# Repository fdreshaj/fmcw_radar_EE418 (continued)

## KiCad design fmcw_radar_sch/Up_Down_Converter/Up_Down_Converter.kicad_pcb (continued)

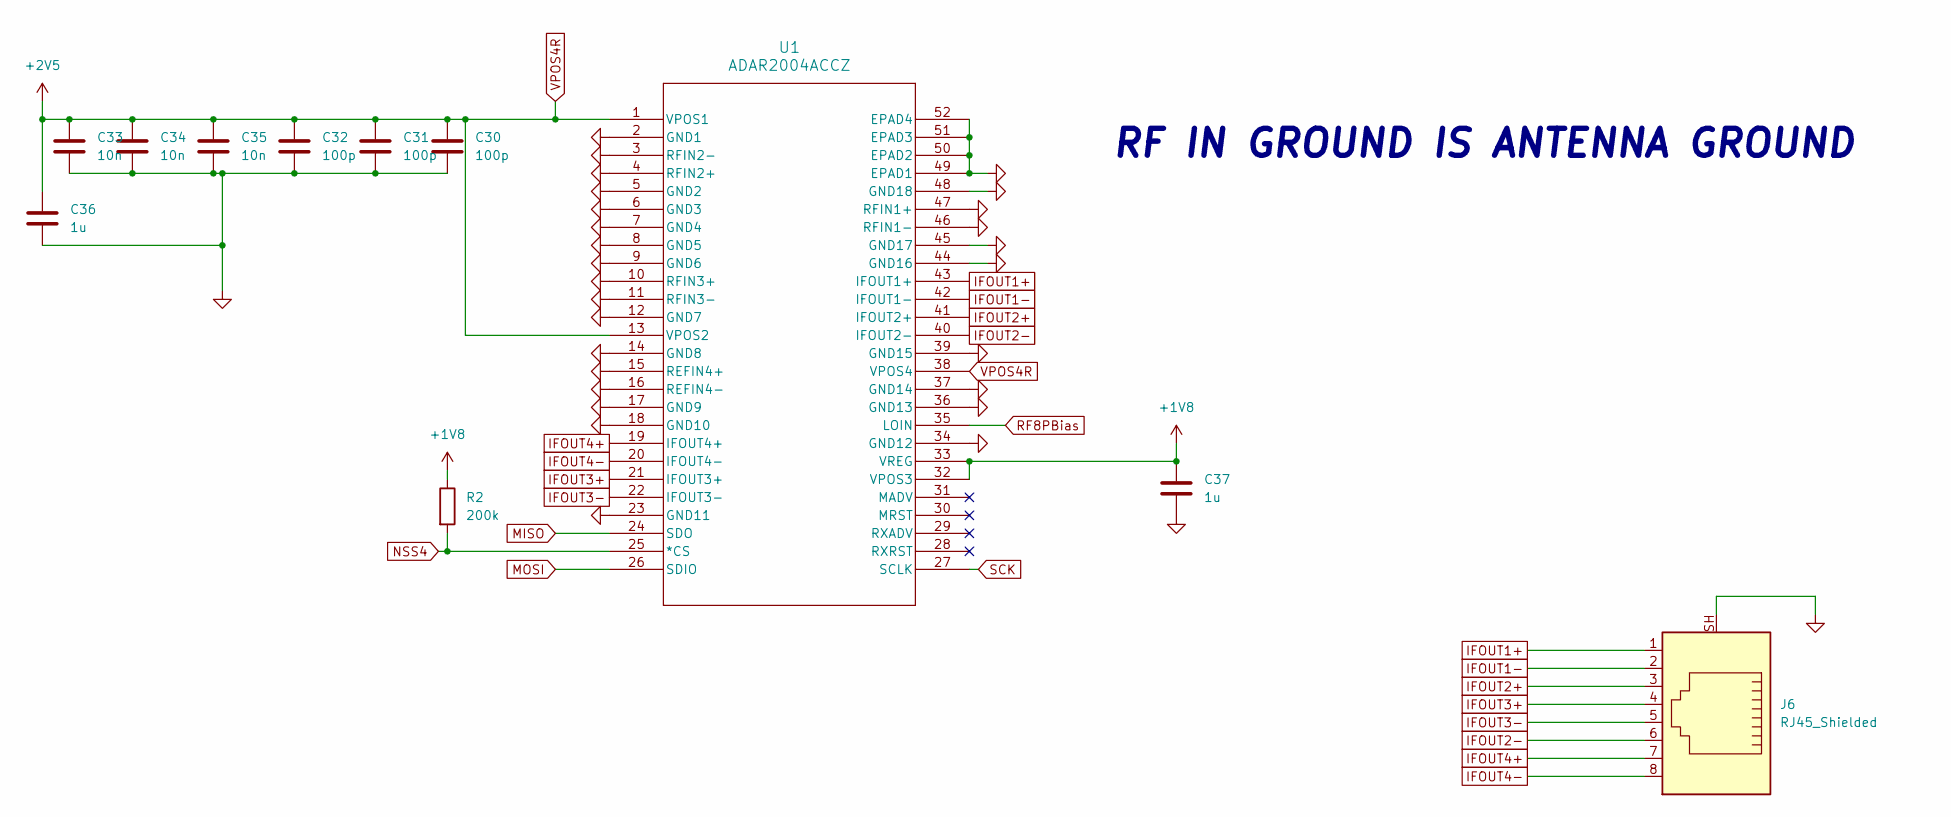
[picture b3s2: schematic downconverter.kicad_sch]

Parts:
C30, C31, C32: 100p; C_0603_1608Metric_Pad1.08x0.95mm_HandSolder
C33, C34, C35: 10n; C_0603_1608Metric_Pad1.08x0.95mm_HandSolder
C36, C37: 1u; C_0603_1608Metric_Pad1.08x0.95mm_HandSolder
J6: RJ45_Shielded; RJ45_Amphenol_RJHSE5380
R2: 200k; R_0603_1608Metric_Pad0.98x0.95mm_HandSolder
U1: ADAR2004ACCZ; LGA_CC_48_2_ADI

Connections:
+1V8: C37.1, R2.1, U1.32 (VPOS3), U1.33 (VREG); also elsewhere on the board
GND: C30.2, C31.2, C32.2, C33.2, C34.2, C35.2, C36.2, C37.2, J6.SH, U1.2 (GND1), U1.3 (RFIN2-), U1.4 (RFIN2+), U1.5 (GND2), U1.6 (GND3), U1.7 (GND4), U1.8 (GND5), U1.9 (GND6), U1.10 (RFIN3+), U1.11 (RFIN3-), U1.12 (GND7), U1.14 (GND8), U1.15 (REFIN4+), U1.16 (REFIN4-), U1.17 (GND9), U1.18 (GND10), U1.23 (GND11), U1.34 (GND12), U1.36 (GND13), U1.37 (GND14), U1.39 (GND15), U1.44 (GND16), U1.45 (GND17), U1.46 (RFIN1-), U1.47 (RFIN1+), U1.48 (GND18), U1.49 (EPAD1), U1.50 (EPAD2), U1.51 (EPAD3), U1.52 (EPAD4); also elsewhere on the board
IFOUT1+: J6.1, U1.43 (IFOUT1+)
IFOUT1-: J6.2, U1.42 (IFOUT1-)
IFOUT2+: J6.3, U1.41 (IFOUT2+)
IFOUT2-: J6.6, U1.40 (IFOUT2-)
IFOUT3+: J6.4, U1.21 (IFOUT3+)
IFOUT3-: J6.5, U1.22 (IFOUT3-)
IFOUT4+: J6.7, U1.19 (IFOUT4+)
IFOUT4-: J6.8, U1.20 (IFOUT4-)
MISO: U1.24 (SDO); also elsewhere on the board
MOSI: U1.26 (SDIO); also elsewhere on the board
NSS4: R2.2, U1.25 (*CS); also elsewhere on the board
SCK: U1.27 (SCLK); also elsewhere on the board
VPOS4R: C30.1, C31.1, C32.1, C33.1, C34.1, C35.1, C36.1, U1.1 (VPOS1), U1.13 (VPOS2), U1.38 (VPOS4); also elsewhere on the board

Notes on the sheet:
RF IN GROUND IS ANTENNA GROUND

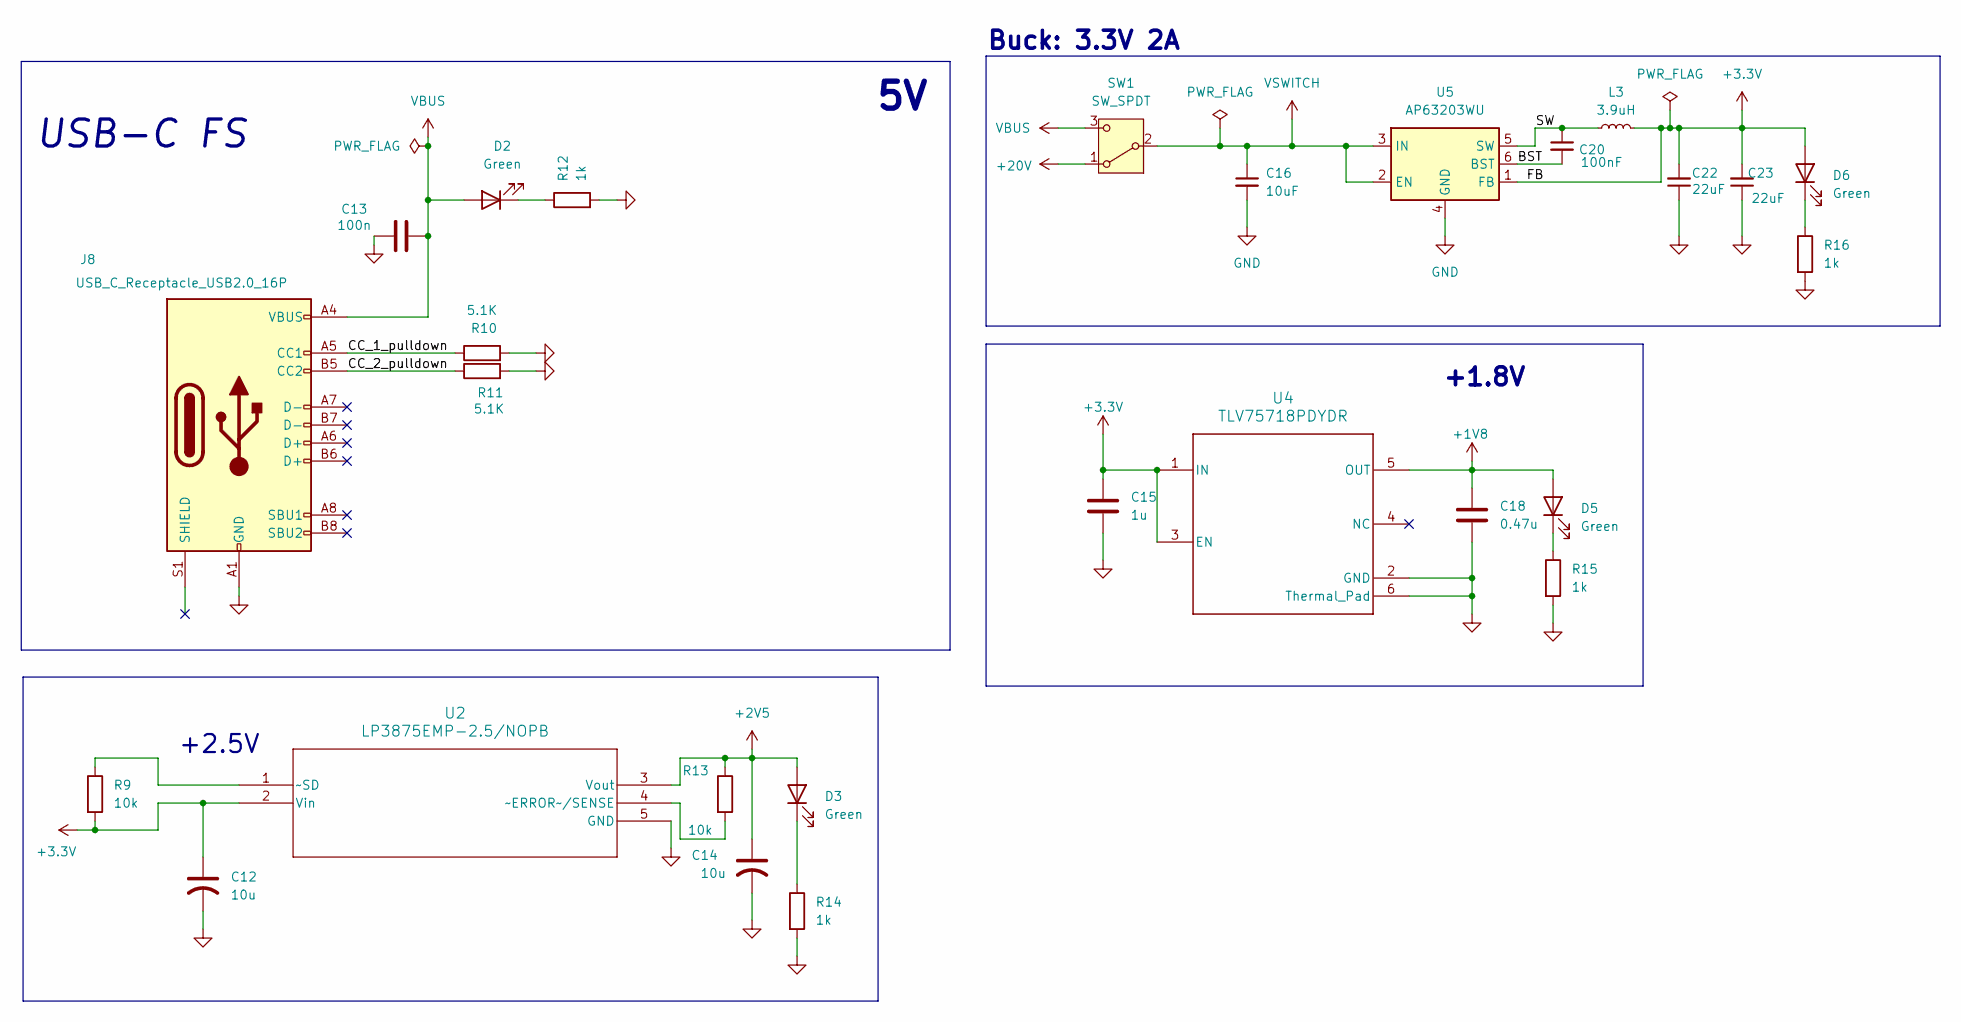
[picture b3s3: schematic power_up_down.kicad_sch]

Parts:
C12, C14: 10u; C_0603_1608Metric_Pad1.08x0.95mm_HandSolder
C13: 100n; C_0603_1608Metric_Pad1.08x0.95mm_HandSolder
C15: 1u; C_0603_1608Metric_Pad1.08x0.95mm_HandSolder
C16: 10uF; C_0603_1608Metric_Pad1.08x0.95mm_HandSolder
C18: 0.47u; C_0603_1608Metric_Pad1.08x0.95mm_HandSolder
C20: 100nF; C_0603_1608Metric_Pad1.08x0.95mm_HandSolder
C22, C23: 22uF; C_0603_1608Metric_Pad1.08x0.95mm_HandSolder
D2, D3, D5, D6: Green; LED_0603_1608Metric_Pad1.05x0.95mm_HandSolder
J8: USB_C_Receptacle_USB2.0_16P; USB_C_Receptacle_G-Switch_GT-USB-7010ASV
L3: 3.9uH; L_Bourns_SDR0604
R9, R13: 10k; R_1206_3216Metric_Pad1.30x1.75mm_HandSolder
R10, R11: 5.1K; R_0603_1608Metric_Pad0.98x0.95mm_HandSolder
R12, R14, R15, R16: 1k; R_0603_1608Metric_Pad0.98x0.95mm_HandSolder
SW1: SW_SPDT; SW_Slide_SPDT_Straight_CK_OS102011MS2Q
U2: LP3875EMP-2.5/NOPB; DNT12_TEX
U4: TLV75718PDYDR; DYD0005A-MFG
U5: AP63203WU; TSOT-23-6

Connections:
+1V8: C18.1, D5.2 (A), U4.5 (OUT); also elsewhere on the board
+3.3V: C12.1, C15.1, C22.2, C23.2, D6.2 (A), L3.2, R9.2, U2.2 (Vin), U4.1 (IN), U4.3 (EN), U5.1 (FB)
+20V: SW1.1 (A); also elsewhere on the board
/Power/BST: C20.2, U5.6 (BST)
/Power/CC_1_pulldown: J8.A5 (CC1), R10.1
/Power/CC_2_pulldown: J8.B5 (CC2), R11.1
/Power/SW: C20.1, L3.1, U5.5 (SW)
GND: C12.2, C13.1, C14.2, C15.2, C16.2, C18.2, C22.1, C23.1, J8.A1 (GND), J8.A12 (GND), J8.B1 (GND), J8.B12 (GND), R10.2, R11.2, R12.2, R14.2, R15.2, R16.2, U2.5 (GND), U4.2 (GND), U4.6 (Thermal_Pad), U5.4 (GND); also elsewhere on the board
unnamed: D2.1 (K), R12.1
unnamed: D3.1 (K), R14.1
unnamed: D5.1 (K), R15.1
unnamed: D6.1 (K), R16.1
unnamed: R13.2, U2.4 (~ERROR~/SENSE)
unnamed: R9.1, U2.1 (~SD)
VBUS: C13.2, D2.2 (A), J8.A4 (VBUS), J8.A9 (VBUS), J8.B4 (VBUS), J8.B9 (VBUS), SW1.3 (C)
VPOS4R: C14.1, D3.2 (A), R13.1, U2.3 (Vout); also elsewhere on the board
VSWITCH: C16.1, SW1.2 (B), U5.2 (EN), U5.3 (IN); also elsewhere on the board

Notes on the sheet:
Buck: 3.3V 2A
+2.5V
USB-C FS
+1.8V

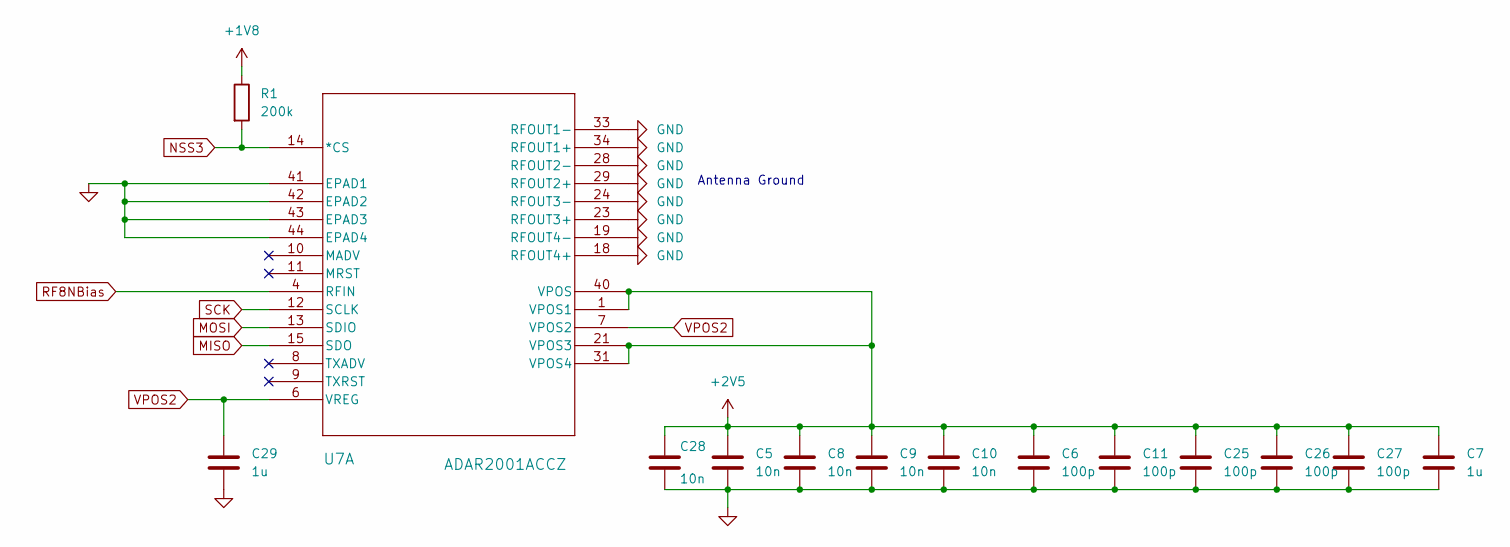
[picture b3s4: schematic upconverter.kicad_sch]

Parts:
C5, C8, C9, C10, C28: 10n; C_0603_1608Metric_Pad1.08x0.95mm_HandSolder
C6, C11, C25, C26, C27: 100p; C_0603_1608Metric_Pad1.08x0.95mm_HandSolder
C7, C29: 1u; C_0603_1608Metric_Pad1.08x0.95mm_HandSolder
R1: 200k; R_0603_1608Metric_Pad0.98x0.95mm_HandSolder
U7: ADAR2001ACCZ; LGA-CC-40-7_ADI

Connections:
+1V8: R1.1; also elsewhere on the board
GND: C5.2, C6.2, C7.2, C8.2, C9.2, C10.2, C11.2, C25.2, C26.2, C27.2, C28.2, C29.2, U7.18 (RFOUT4+), U7.19 (RFOUT4-), U7.23 (RFOUT3+), U7.24 (RFOUT3-), U7.28 (RFOUT2-), U7.29 (RFOUT2+), U7.33 (RFOUT1-), U7.34 (RFOUT1+), U7.41 (EPAD1), U7.42 (EPAD2), U7.43 (EPAD3), U7.44 (EPAD4); also elsewhere on the board
MISO: U7.15 (SDO); also elsewhere on the board
MOSI: U7.13 (SDIO); also elsewhere on the board
NSS3: R1.2, U7.14 (*CS); also elsewhere on the board
SCK: U7.12 (SCLK); also elsewhere on the board
VPOS2: C29.1, U7.6 (VREG), U7.7 (VPOS2)
VPOS4R: C5.1, C6.1, C7.1, C8.1, C9.1, C10.1, C11.1, C25.1, C26.1, C27.1, C28.1, U7.1 (VPOS1), U7.21 (VPOS3), U7.31 (VPOS4), U7.40 (VPOS); also elsewhere on the board

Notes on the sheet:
Antenna Ground

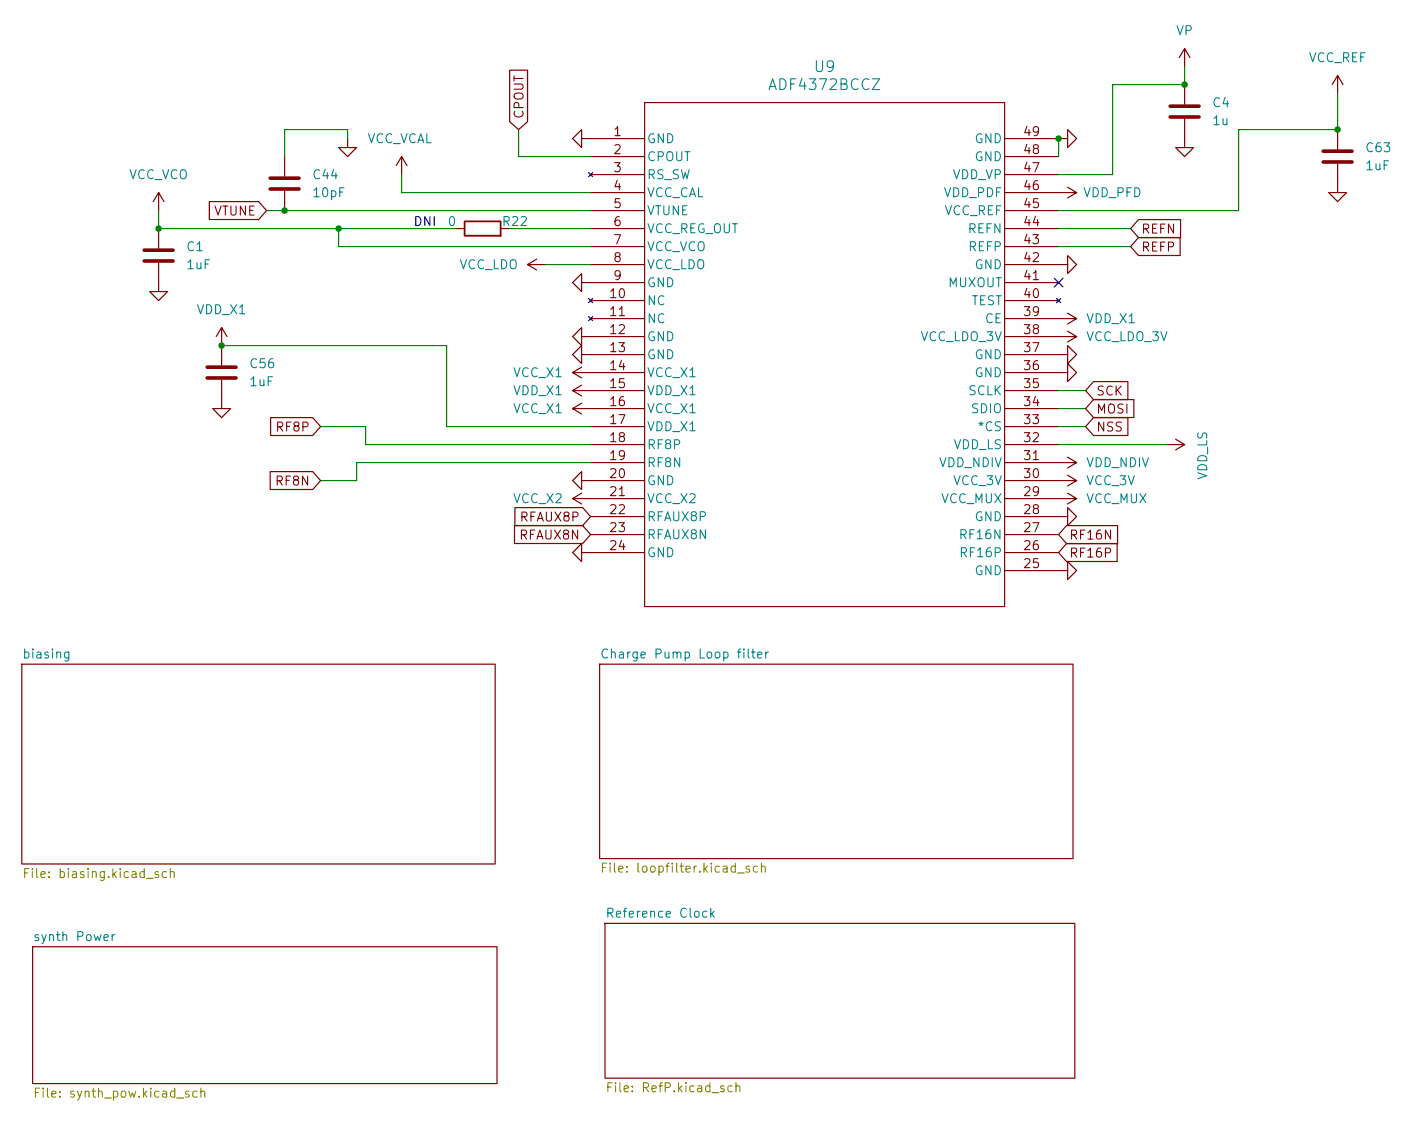
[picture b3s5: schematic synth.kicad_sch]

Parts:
C1, C56, C63: 1uF; C_0603_1608Metric_Pad1.08x0.95mm_HandSolder
C4: 1u; C_0603_1608Metric_Pad1.08x0.95mm_HandSolder
C44: 10pF; C_0603_1608Metric_Pad1.08x0.95mm_HandSolder
R22: 0; R_0603_1608Metric_Pad0.98x0.95mm_HandSolder
U9: ADF4372BCCZ; CC-48-4_ADI

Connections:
CPOUT: U9.2 (CPOUT); also elsewhere on the board
GND: C1.2, C4.2, C44.1, C56.2, C63.2, U9.1 (GND), U9.9 (GND), U9.12 (GND), U9.13 (GND), U9.20 (GND), U9.24 (GND), U9.25 (GND), U9.28 (GND), U9.36 (GND), U9.37 (GND), U9.42 (GND), U9.48 (GND), U9.49 (GND); also elsewhere on the board
MOSI: U9.34 (SDIO); also elsewhere on the board
NSS: U9.33 (*CS); also elsewhere on the board
unnamed: R22.2, U9.6 (VCC_REG_OUT)
REFP: U9.43 (REFP); also elsewhere on the board
RF16N: U9.27 (RF16N); also elsewhere on the board
RF16P: U9.26 (RF16P); also elsewhere on the board
RFAUX8N: U9.23 (RFAUX8N); also elsewhere on the board
RFAUX8P: U9.22 (RFAUX8P); also elsewhere on the board
SCK: U9.35 (SCLK); also elsewhere on the board
VCC_3V: C56.1, U9.4 (VCC_CAL), U9.14 (VCC_X1), U9.15 (VDD_X1), U9.16 (VCC_X1), U9.17 (VDD_X1), U9.21 (VCC_X2), U9.29 (VCC_MUX), U9.30 (VCC_3V), U9.31 (VDD_NDIV), U9.32 (VDD_LS), U9.39 (CE); also elsewhere on the board
VCC_LDO: U9.8 (VCC_LDO); also elsewhere on the board
VCC_LDO_3V: C4.1, C63.1, U9.38 (VCC_LDO_3V), U9.45 (VCC_REF), U9.46 (VDD_PDF), U9.47 (VDD_VP); also elsewhere on the board
VCC_VCO: C1.1, R22.1, U9.7 (VCC_VCO); also elsewhere on the board
VTUNE: C44.2, U9.5 (VTUNE); also elsewhere on the board

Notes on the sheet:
DNI

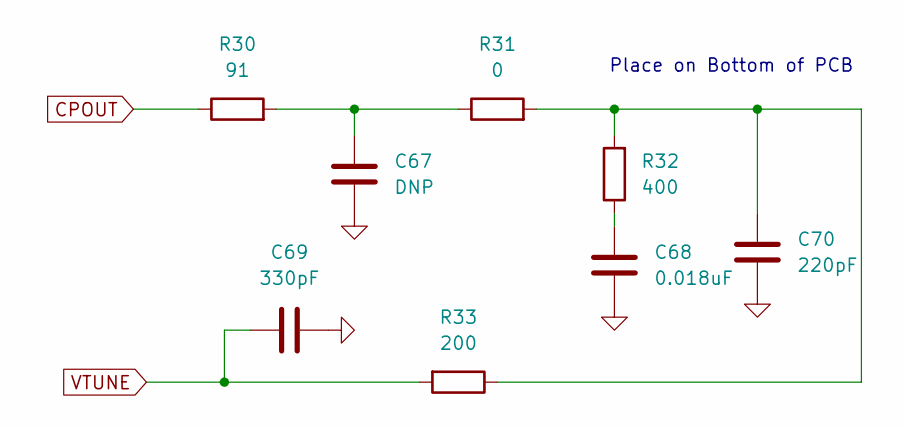
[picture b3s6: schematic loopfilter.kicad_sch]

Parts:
C67: DNP; C_0603_1608Metric_Pad1.08x0.95mm_HandSolder
C68: 0.018uF; C_0603_1608Metric_Pad1.08x0.95mm_HandSolder
C69: 330pF; C_0603_1608Metric_Pad1.08x0.95mm_HandSolder
C70: 220pF; C_0603_1608Metric_Pad1.08x0.95mm_HandSolder
R30: 91; R_0603_1608Metric_Pad0.98x0.95mm_HandSolder
R31: 0; R_0603_1608Metric_Pad0.98x0.95mm_HandSolder
R32: 400; R_0603_1608Metric_Pad0.98x0.95mm_HandSolder
R33: 200; R_0603_1608Metric_Pad0.98x0.95mm_HandSolder

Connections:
CPOUT: R30.1; also elsewhere on the board
GND: C67.2, C68.2, C69.2, C70.2; also elsewhere on the board
unnamed: C67.1, R30.2, R31.1
unnamed: C68.1, R32.1
unnamed: C70.1, R31.2, R32.2, R33.1
VTUNE: C69.1, R33.2; also elsewhere on the board

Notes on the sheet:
Place on Bottom of PCB

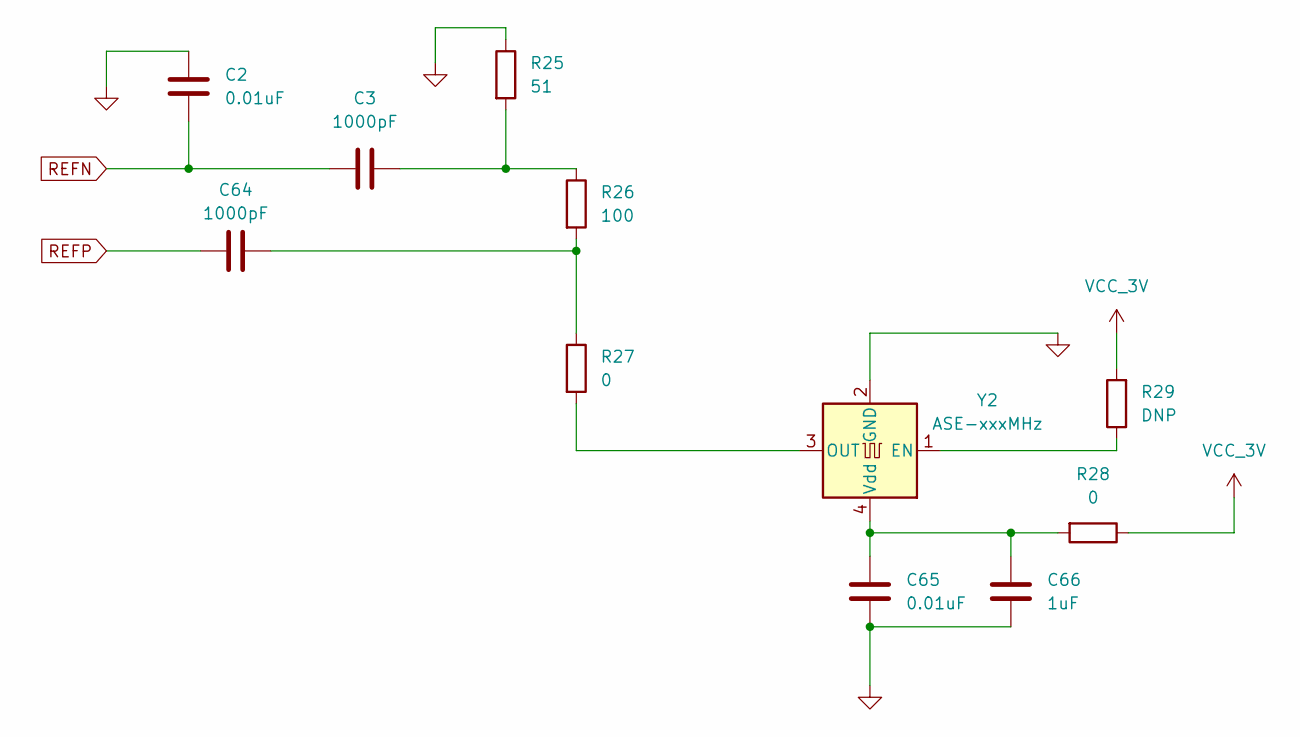
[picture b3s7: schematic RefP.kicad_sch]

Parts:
C2, C65: 0.01uF; C_0603_1608Metric_Pad1.08x0.95mm_HandSolder
C3, C64: 1000pF; C_0603_1608Metric_Pad1.08x0.95mm_HandSolder
C66: 1uF; C_0603_1608Metric_Pad1.08x0.95mm_HandSolder
R25: 51; R_0603_1608Metric_Pad0.98x0.95mm_HandSolder
R26: 100; R_0603_1608Metric_Pad0.98x0.95mm_HandSolder
R27, R28: 0; R_0603_1608Metric_Pad0.98x0.95mm_HandSolder
R29: DNP; R_0603_1608Metric_Pad0.98x0.95mm_HandSolder
Y2: ASE-xxxMHz; Oscillator_SMD_Abracon_ASE-4Pin_3.2x2.5mm

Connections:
GND: C2.1, C65.2, C66.2, R25.1, Y2.2 (GND); also elsewhere on the board
unnamed: C64.1, R26.2, R27.1
unnamed: R29.1, Y2.1 (EN)
unnamed: R27.2, Y2.3 (OUT)
unnamed: C65.1, C66.1, R28.2, Y2.4 (Vdd)
REFP: C64.2; also elsewhere on the board
VCC_3V: R28.1, R29.2; also elsewhere on the board

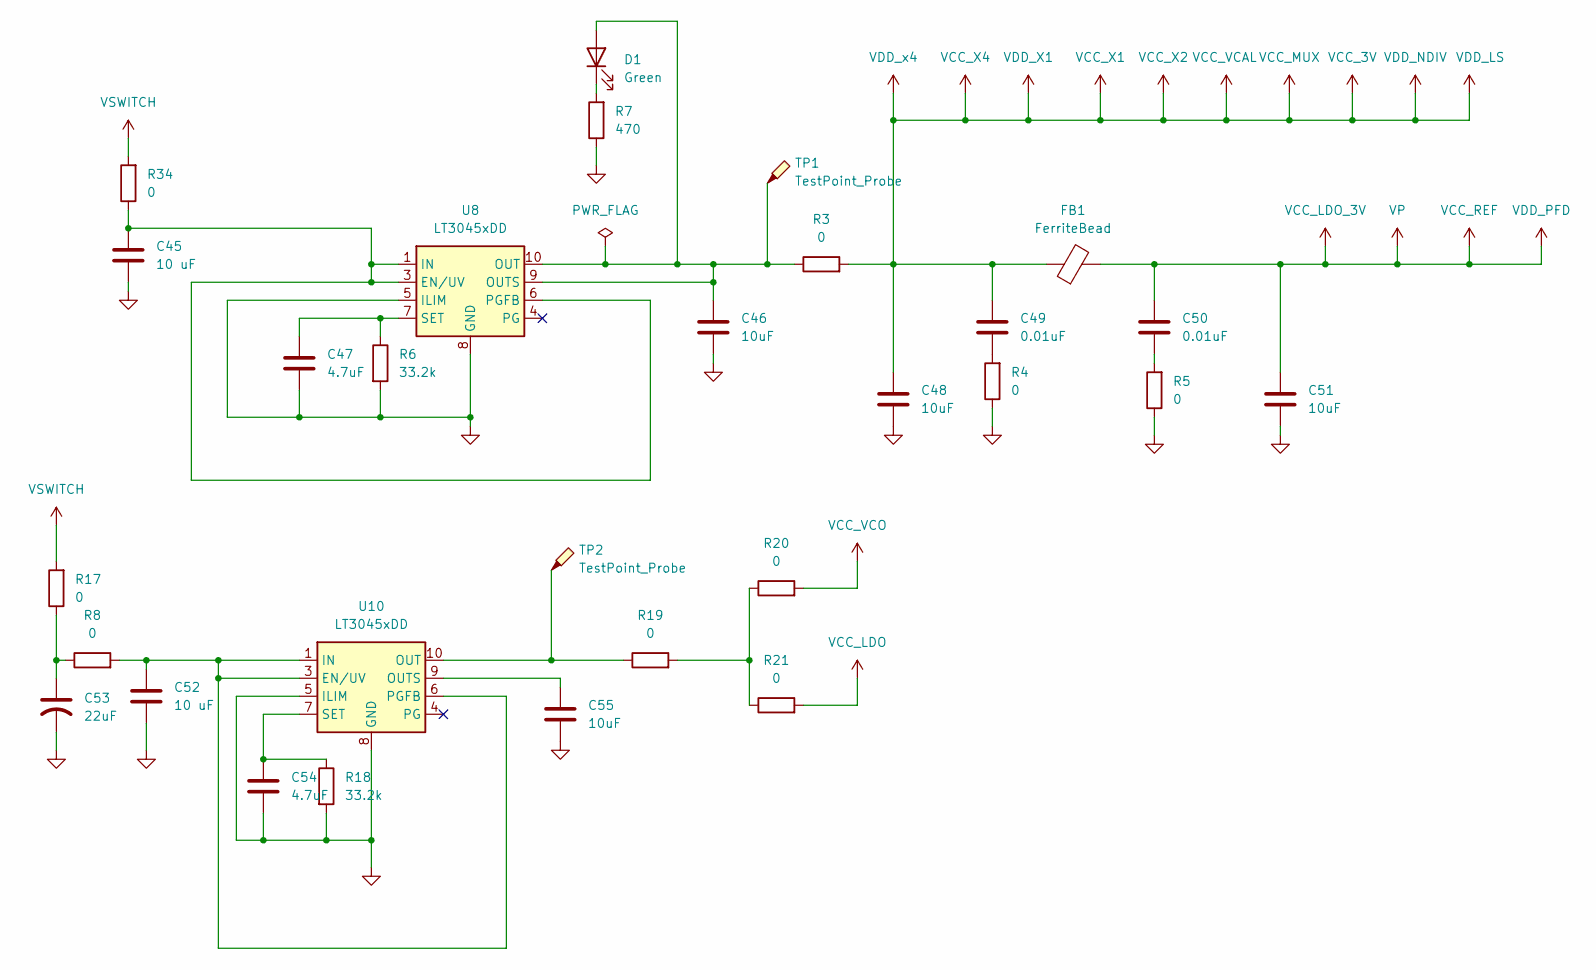
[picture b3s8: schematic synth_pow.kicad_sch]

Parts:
C45, C52: 10 uF; C_0603_1608Metric_Pad1.08x0.95mm_HandSolder
C46, C48, C51, C55: 10uF; C_0603_1608Metric_Pad1.08x0.95mm_HandSolder
C47, C54: 4.7uF; C_0603_1608Metric_Pad1.08x0.95mm_HandSolder
C49, C50: 0.01uF; C_0603_1608Metric_Pad1.08x0.95mm_HandSolder
C53: 22uF; C_0603_1608Metric_Pad1.08x0.95mm_HandSolder
D1: Green; LED_0603_1608Metric_Pad1.05x0.95mm_HandSolder
FB1: FerriteBead; L_0603_1608Metric_Pad1.05x0.95mm_HandSolder
R3, R4, R5, R8, R17, R19, R20, R21, R34: 0; R_0603_1608Metric_Pad0.98x0.95mm_HandSolder
R6, R18: 33.2k; R_0603_1608Metric_Pad0.98x0.95mm_HandSolder
R7: 470; R_0603_1608Metric_Pad0.98x0.95mm_HandSolder
TP1, TP2: TestPoint_Probe; TestPoint_Loop_D2.50mm_Drill1.0mm
U8, U10: LT3045xDD; DFN-10-1EP_3x3mm_P0.5mm_EP1.65x2.38mm

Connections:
GND: C45.2, C46.2, C47.2, C48.2, C51.2, C52.2, C53.2, C54.2, C55.2, R4.1, R5.1, R6.2, R7.1, R18.2, U8.5 (ILIM), U8.8 (GND), U8.11 (GND), U10.5 (ILIM), U10.8 (GND), U10.11 (GND); also elsewhere on the board
unnamed: C49.2, R4.2
unnamed: C50.2, R5.2
unnamed: C53.1, R8.1, R17.1
unnamed: C46.1, D1.2 (A), R3.1, TP1.1, U8.9 (OUTS), U8.10 (OUT)
unnamed: D1.1 (K), R7.2
unnamed: R19.2, R20.1, R21.1
unnamed: C45.1, R34.1, U8.1 (IN), U8.2 (IN), U8.3 (EN/UV), U8.6 (PGFB)
unnamed: C47.1, R6.1, U8.7 (SET)
unnamed: C52.1, R8.2, U10.1 (IN), U10.2 (IN), U10.3 (EN/UV), U10.6 (PGFB)
unnamed: R19.1, TP2.1, U10.10 (OUT)
unnamed: C55.1, U10.9 (OUTS)
unnamed: C54.1, R18.1, U10.7 (SET)
VCC_3V: C48.1, C49.1, FB1.1, R3.2; also elsewhere on the board
VCC_LDO: R21.2; also elsewhere on the board
VCC_LDO_3V: C50.1, C51.1, FB1.2; also elsewhere on the board
VCC_VCO: R20.2; also elsewhere on the board
VSWITCH: R17.2, R34.2; also elsewhere on the board

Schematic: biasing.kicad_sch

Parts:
C59: pF; C_0603_1608Metric_Pad1.08x0.95mm_HandSolder
C60, C61, C62: 10pF; C_0603_1608Metric_Pad1.08x0.95mm_HandSolder
J13, J15, J16, J17: Conn_Coaxial; SMA_Amphenol_132289_EdgeMount
L7, L8: 7.4nH; L_0603_1608Metric_Pad1.05x0.95mm_HandSolder

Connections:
GND: C59.2, C62.2, J13.2 (Ext), J15.2 (Ext), J16.2 (Ext), J17.2 (Ext); also elsewhere on the board
unnamed: C60.2, J13.1 (In)
unnamed: C61.2, J15.1 (In)
RF16N: J16.1 (In); also elsewhere on the board
RF16P: J17.1 (In); also elsewhere on the board
RFAUX8N: C60.1, L7.2; also elsewhere on the board
RFAUX8P: C61.1, L8.1; also elsewhere on the board
VCC_3V: C59.1, C62.1, L7.1, L8.2; also elsewhere on the board

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
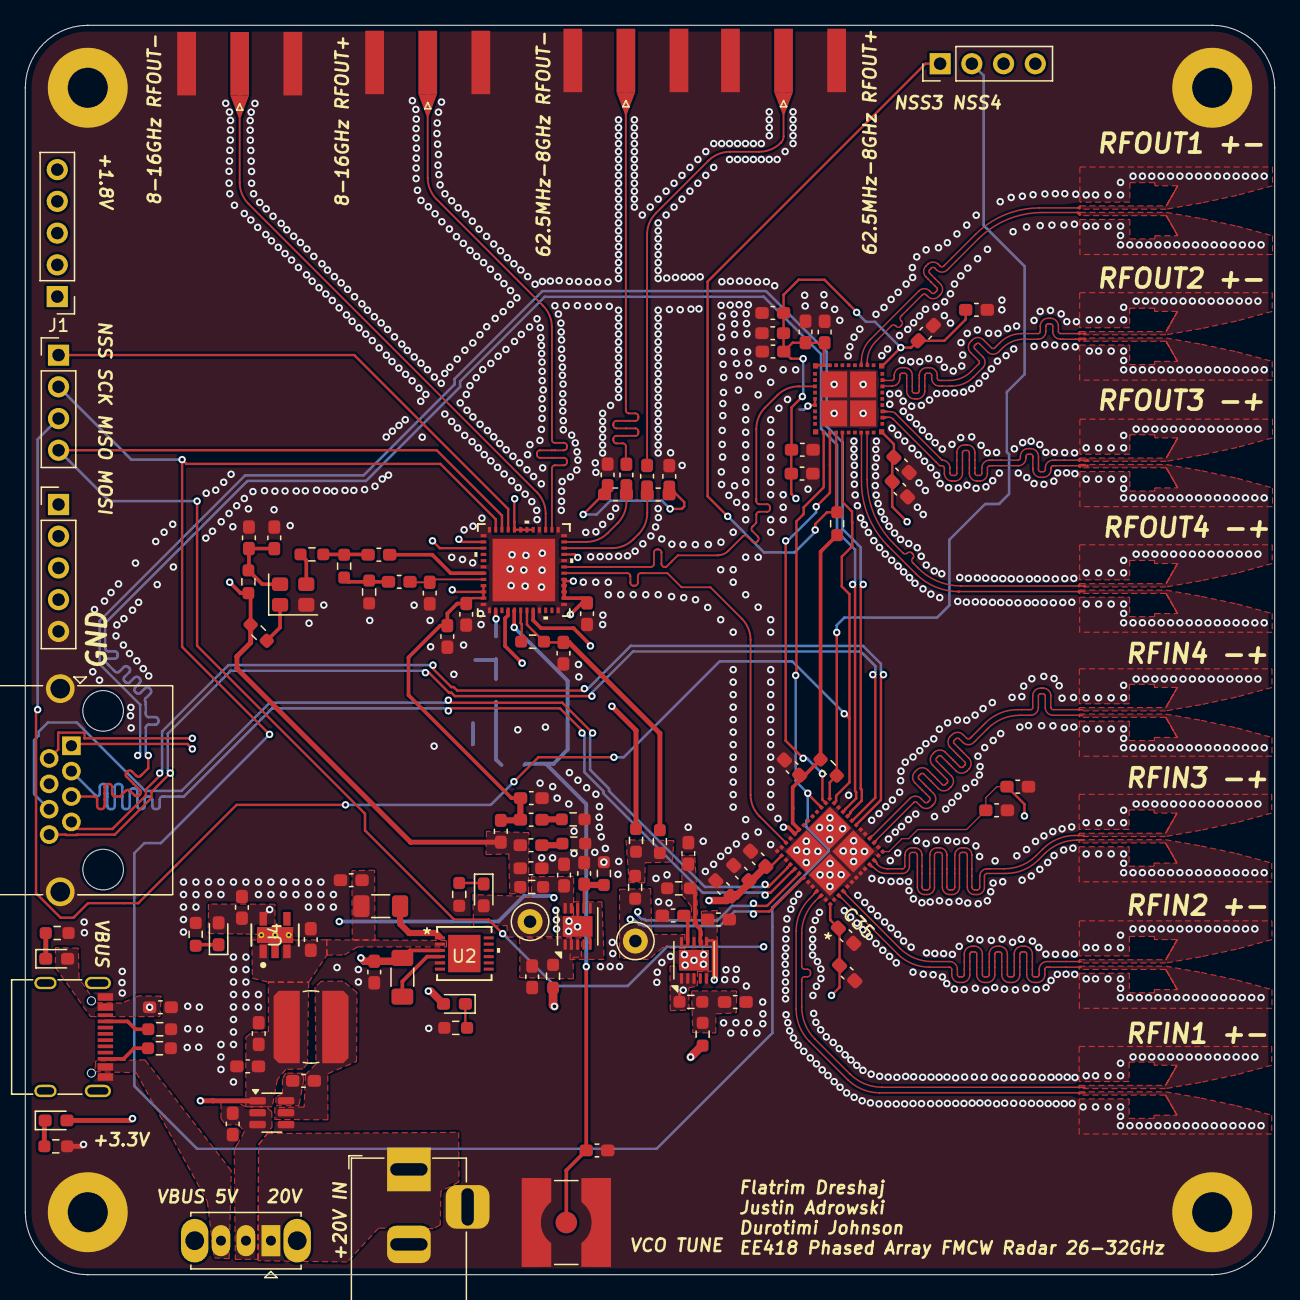
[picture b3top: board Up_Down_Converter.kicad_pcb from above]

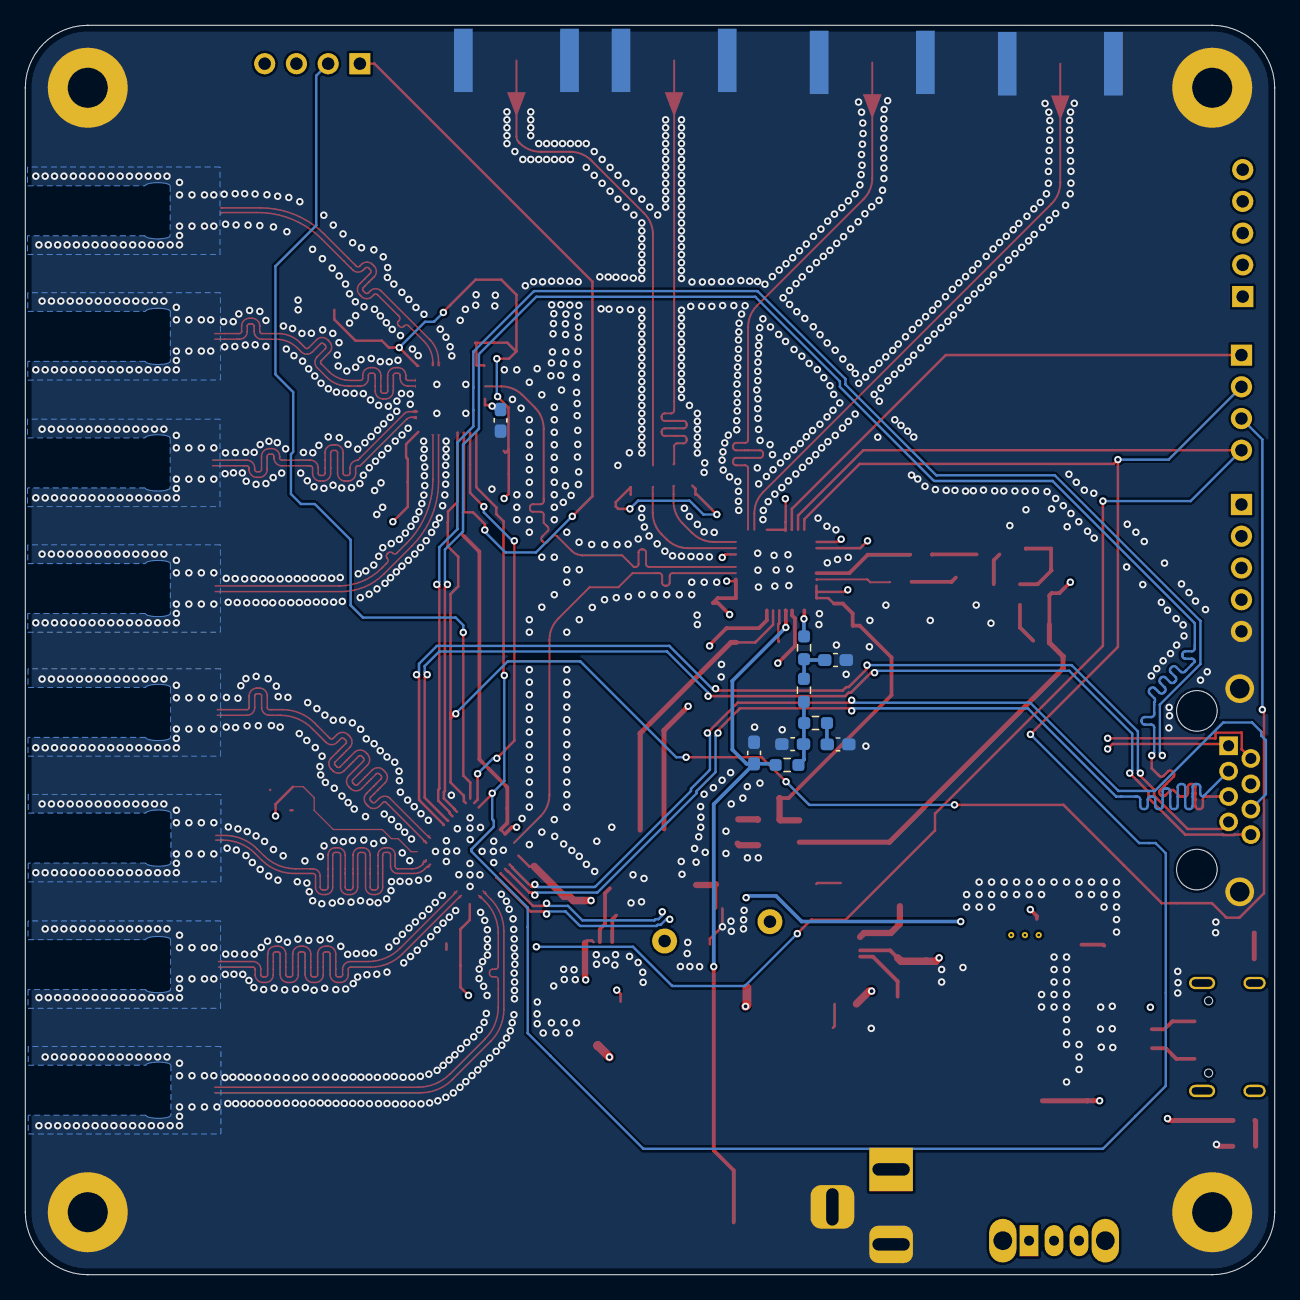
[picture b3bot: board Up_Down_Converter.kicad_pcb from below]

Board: 4 copper layers, 100.0 x 100.0 mm, 127 parts (9 on the bottom side), 69 nets.

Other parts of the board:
J5, J14: Conn_01x05_Pin; PinHeader_1x05_P2.54mm_Vertical

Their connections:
+1V8: J5.5; also elsewhere on the board
GND: J14.5; also elsewhere on the board
VPOS4R: J14.1; also elsewhere on the board

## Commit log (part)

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2026-01-27 sys level overview
    sys level overview
2026-01-27 changes
    changes
2026-01-27 added kicad project
    added kicad project
2026-01-28 initial parts search
    initial parts search
2026-02-02 README.md
2026-03-02 KiCAD files
    What I currently have for the KiCAD of the transmission. Let me know if there's any issues
2026-03-18 minor changes
    minorchanges
2026-03-19 added MCU PSU VCO
2026-03-24 board changes
    board changes
2026-03-27 Add files via upload
    The pcb_editor file in this group has the profile for the vivaldi I designed in CST. It uses the standard 4 layer stackup from JLCPCB's controlled impedance stackup.
2026-03-29 Layout of controller board
2026-03-30 Routing
    Routing
2026-03-30 RF Board Sch
    RF Board Sch
2026-03-30 layout
2026-04-01 rf changes
    rf changes
2026-04-01 Create FMCW_Radar.ioc
    Added the STM32CubeIDE project for the Firmware
2026-04-02 Set up the project file
    Set up files in cubeide and cubemx within a github folder for us to edit
2026-04-02 Added pin functions
2026-04-02 Program DAC Functions added
    Added first source and header files with code for programming the DAC to sawtooth sweep from 0-3.3V
2026-04-02 initial
    initial
2026-04-06 a lot of updates
    usb power delivery + finishing touches
2026-04-06 Silkscreen finishing
    Silkscreen finishting
2026-04-06 Gerbers
    Gerbers
2026-04-07 final changes to RF board
    final changes to RF board + grbs
2026-04-08 changes from yesterday
    changes from yesterday
2026-04-25 Add SPI driver files
2026-04-27 Added functions to .c src files and got project to compile
2026-05-03 Add FMCW radar source files
2026-05-04 Remove tracked build and metadata files
